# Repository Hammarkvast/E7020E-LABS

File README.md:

# E7020E-LABS
Laboratory assignments for the course E7020E at Luleå University of Technology

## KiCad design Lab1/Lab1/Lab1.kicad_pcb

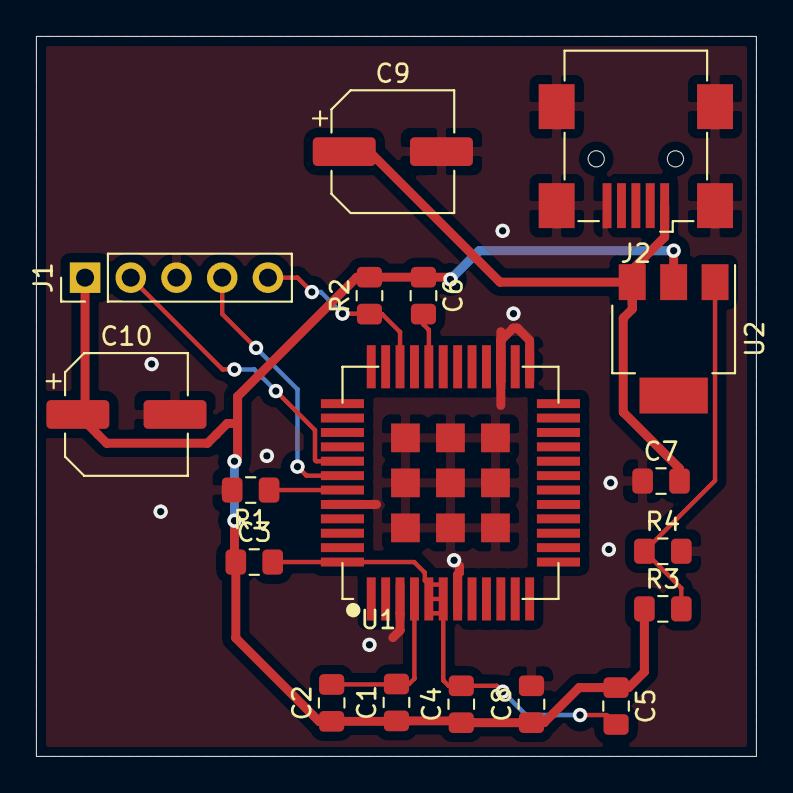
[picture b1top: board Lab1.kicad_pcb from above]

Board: 2 copper layers, 40.0 x 40.0 mm, 18 parts (0 on the bottom side), 11 nets.

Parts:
C1, C2, C3, C4, C5, C6: 100n; C_0805_2012Metric_Pad1.15x1.40mm_HandSolder
C7: 10uF; C_0805_2012Metric_Pad1.15x1.40mm_HandSolder
C8: 100uF; C_0805_2012Metric_Pad1.15x1.40mm_HandSolder
C9, C10: 10u; CP_Elec_6.3x7.7
J1: Conn_01x05_Male; PinHeader_1x05_P2.54mm_Vertical
J2: USB_OTG; USB_Mini-B_Wuerth_65100516121_Horizontal
R1, R2: 10k; R_0805_2012Metric_Pad1.15x1.40mm_HandSolder
R3: 333000; R_0805_2012Metric_Pad1.15x1.40mm_HandSolder
R4: 10000; R_0805_2012Metric_Pad1.15x1.40mm_HandSolder
U1: CMWX1ZZABZ-078; CMWX1ZZABZ_longer_pads
U2: LM1117ADJ; SOT-223

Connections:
+3V3: C1.1, C2.1, C3.1, C4.1, C5.1, C6.1, C8.1, C10.1, J1.1, R2.2, R3.1, U2.2
+5V: C7.2, C9.1, J2.1, U2.3
GND: C7.1, C8.2, C9.2, C10.2, J1.3, J2.5, J2.6, R1.2, R4.2, U1.3, U1.7, U1.25, U1.27, U1.44, U1.49, U1.50, U1.51, U1.52, U1.53, U1.54, U1.55, U1.56, U1.57
unnamed: C1.2, C2.2, U1.4
unnamed: C3.2, C4.2, C5.2, U1.5, U1.6, U1.48
unnamed: C6.2, U1.32
unnamed: J1.2, U1.41
unnamed: J1.4, U1.42
unnamed: J1.5, R2.1, U1.34
unnamed: R1.1, U1.43
unnamed: R3.2, R4.1, U2.1

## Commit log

2020-01-28 Lab 1 DONE
2020-02-10 Lab 2 DONE
